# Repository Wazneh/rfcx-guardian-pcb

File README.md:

# rfcx-guardian-pcb
Hardware PCB designs for RFCx Guardians

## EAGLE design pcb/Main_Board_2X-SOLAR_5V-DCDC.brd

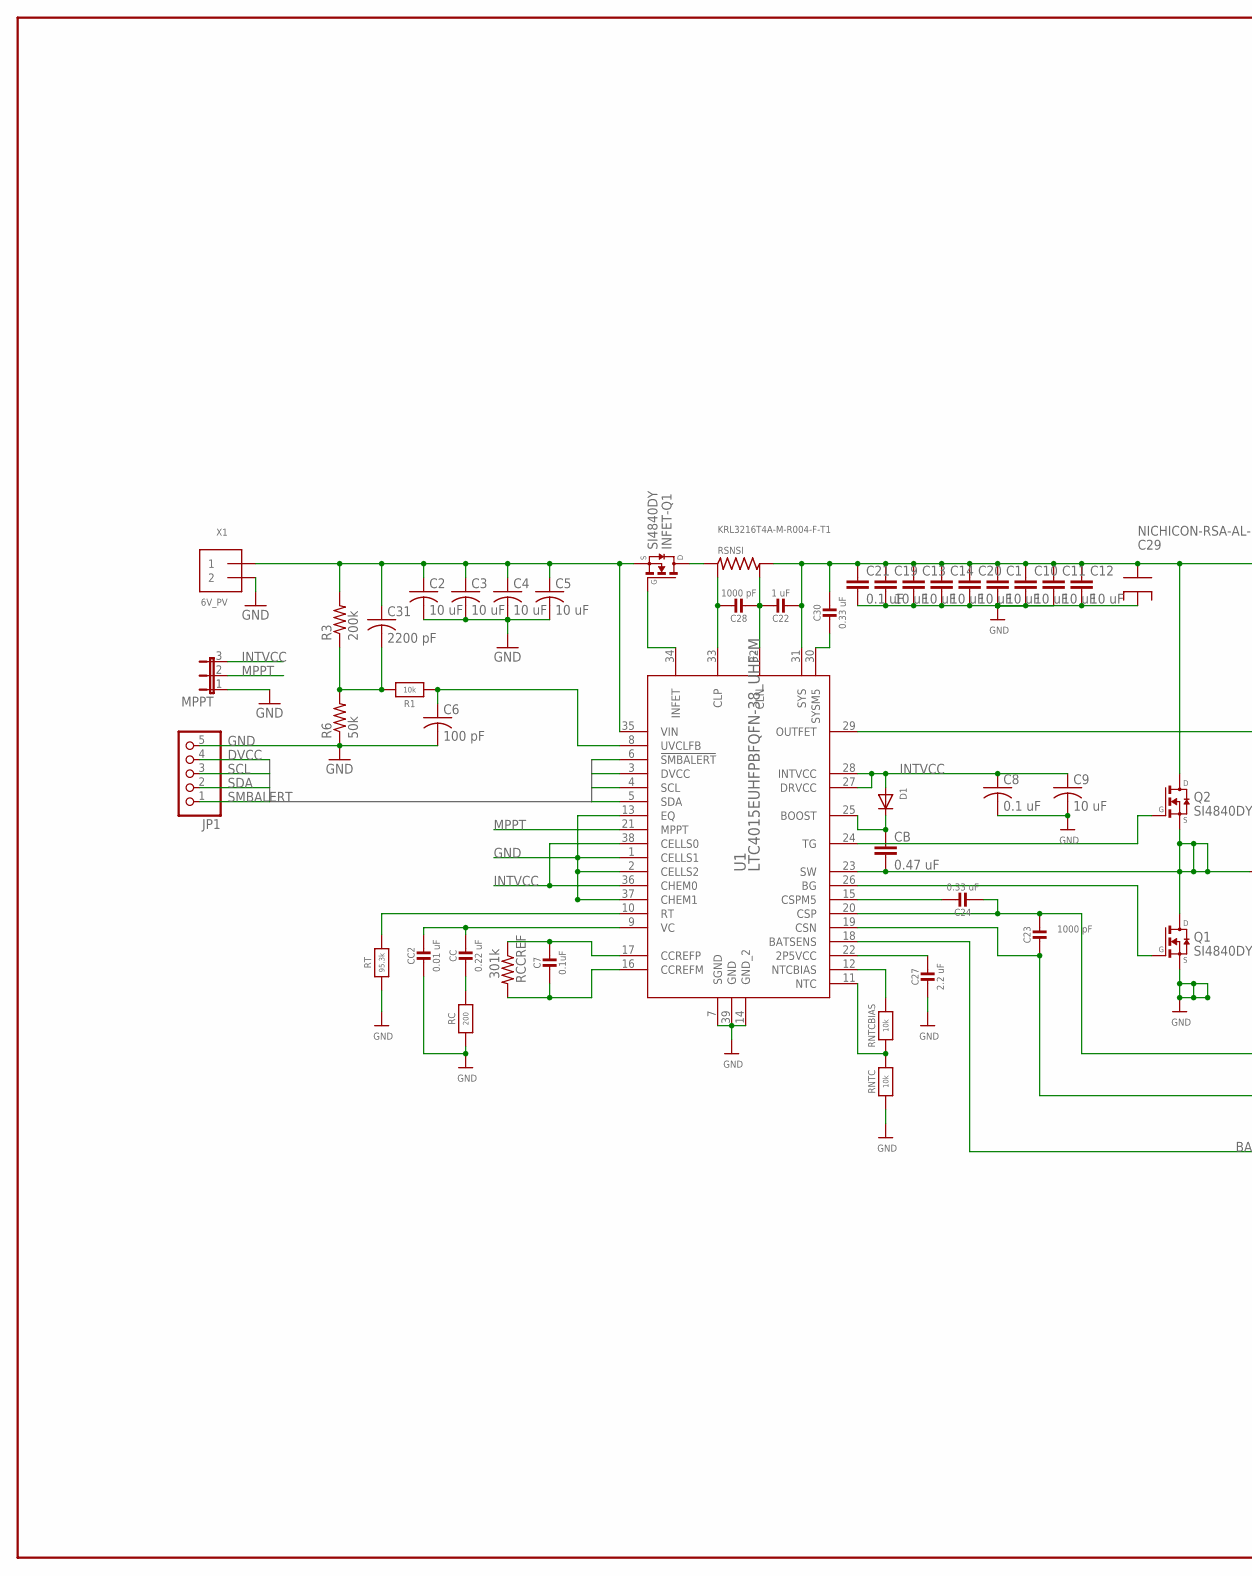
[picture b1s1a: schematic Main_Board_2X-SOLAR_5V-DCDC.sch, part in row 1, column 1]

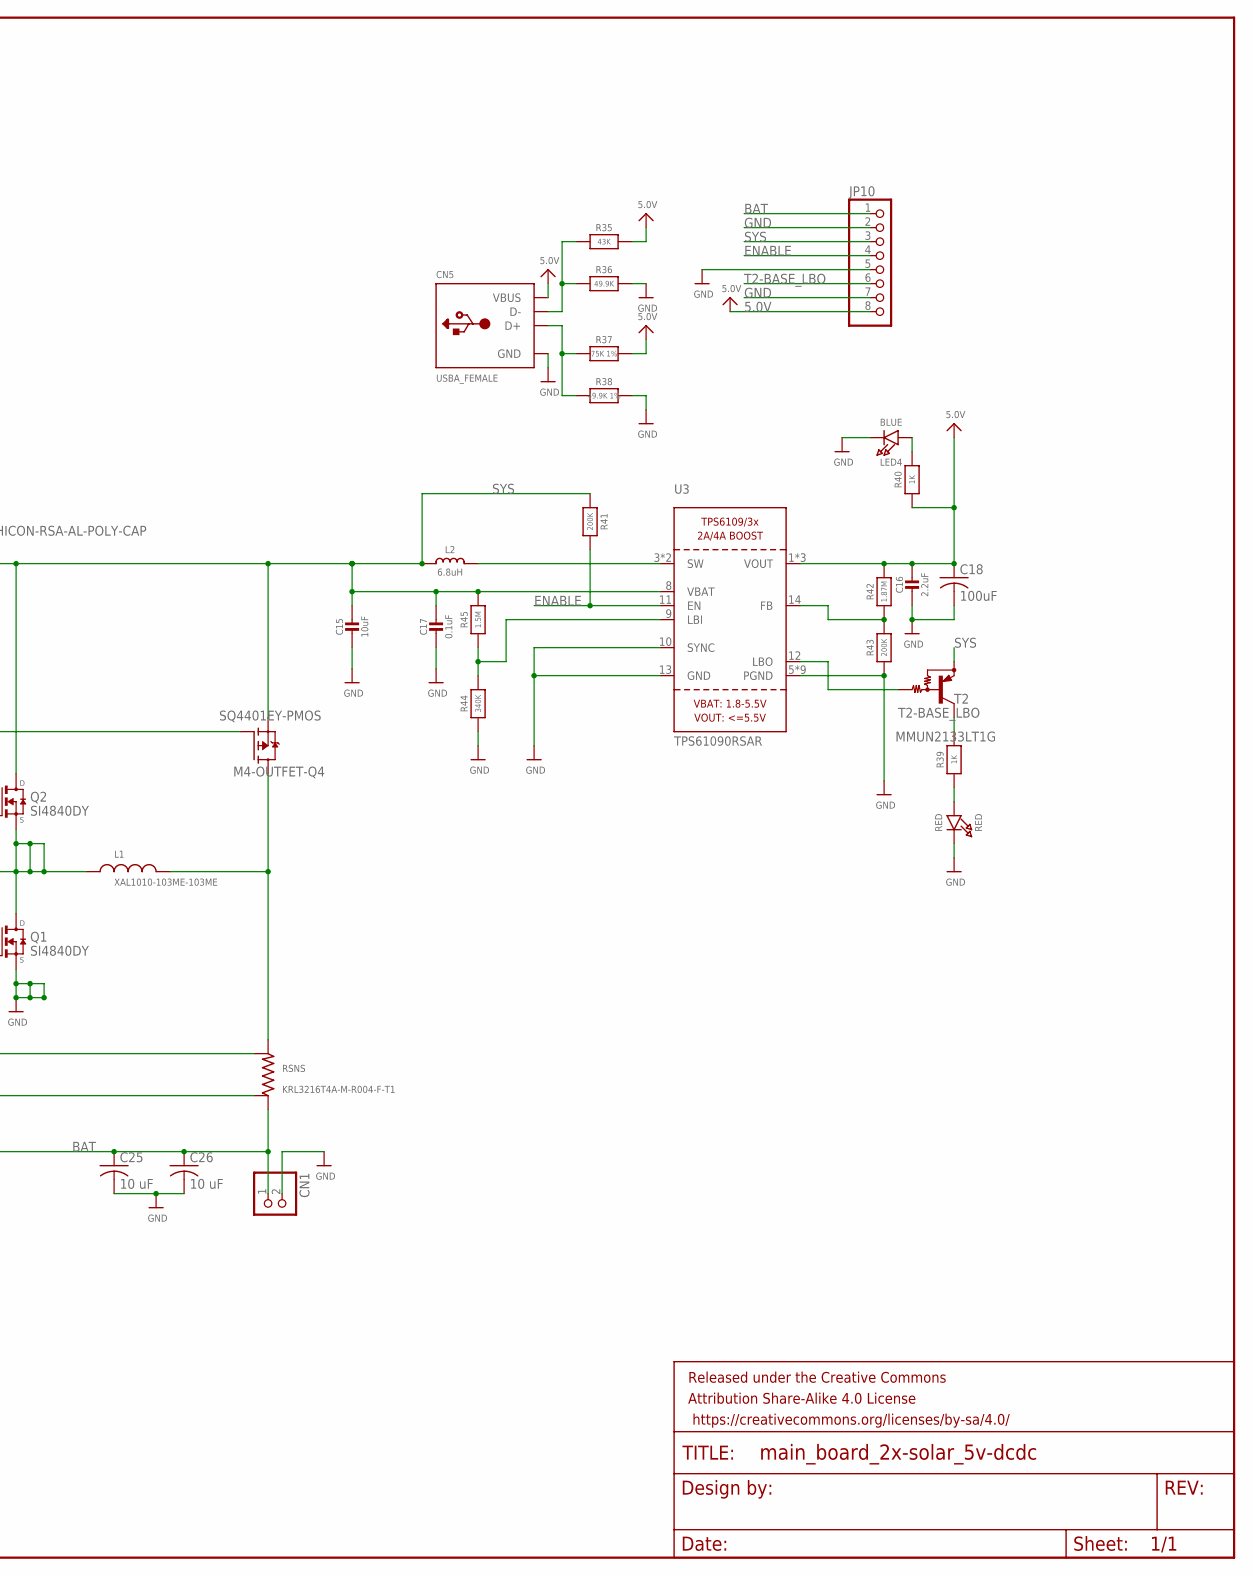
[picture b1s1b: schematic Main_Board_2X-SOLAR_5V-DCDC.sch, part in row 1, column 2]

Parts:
C1, C10, C11, C12, C13, C14, C19, C20, C25, C26: 10 uF; C1206
C2, C3, C4, C5, C9: 10 uF; C0805
C6: 100 pF; C0805
C7, C17: 0.1uF; 0805_10MGAP
C8: 0.1 uF; C0805
C15: 10uF; 0805-NO
C16: 2.2uF; 0805-NO
C18: 100uF; C1210
C21: 0.1 uF; C1206
C22: 1 uF; 0805-NO
C23, C28: 1000 pF; 0805-NO
C24, C30: 0.33 uF; 0805-NO
C27: 2.2 uF; 0805-NO
C29: NICHICON-RSA-AL-POLY-CAP; RSA-CAP-SMD
C31: 2200 pF; C0805
CB: 0.47 uF; C1206
CC: 0.22 uF; 0805-NO
CC2: 0.01 uF; 0805-NO
CN1: JST_2PIN-THM; JST-PH-2-THM
CN5: USBA_FEMALE; USB_HOST-PTH
D1: DIODESOD-123; SOD-123
FRAME1: FRAME-LEDGER; CREATIVE_COMMONS
INFET-Q1: SI4840DY; SO08-E3
JP1: PINHD-1X5; 1X05
JP10: HEADER-1X8ROUND; 1X08_ROUND
L1: XAL1010-103ME-103ME; XAL1010
L2: 6.8uH; INDUCTOR_5X5MM_TDK_VLC5045
LED4: BLUE; CHIPLED_0805_NOOUTLINE
M4-OUTFET-Q4: SQ4401EY-PMOS; SO08-E3
MPPT: JP2E; JP2
Q1, Q2: SI4840DY; SO08-E3
R1: 10k; _0805MP
R3: 200k; R0805
R6: 50k; R0805
R35: 43K; 0805-NO
R36: 49.9K; 0805-NO
R37: 75K 1%; 0805-NO
R38: 49.9K 1%; 0805-NO
R39, R40: 1K; 0805-NO
R41, R43: 200K; 0805-NO
R42: 1.87M; 0805-NO
R44: 340K; _0805MP
R45: 1.5M; _0805MP
RC: 200; 0805-NO
RCCREF: 301k; R0805
RED: RED; CHIPLED_0805_NOOUTLINE
RNTC: 10k; _0805MP
RNTCBIAS: 10k; _0805MP
RSNS: KRL3216T4A-M-R004-F-T1; 4-TERM-RESISTOR-SUMUSU
RSNSI: KRL3216T4A-M-R004-F-T1; 4-TERM-RESISTOR-SUMUSU
RT: 95.3k; 0805-NO
T2: MMUN2133LT1G; SC59-BEC
U1: LTC4015EUHFPBFQFN-38_UHF-M; QFN-38_UHF-M
U3: TPS61090RSAR; PVQFN-16
X1: 6V_PV; TERMBLOCK_1X2-3.5MM

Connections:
2P5VCC: C27.1, U1.22 (2P5VCC)
5.0V: C16.1, C18.1, CN5.VBUS, JP10.8, R35.2, R37.2, R40.1, R42.2, U3.1 (VOUT), U3.15 (VOUT), U3.16 (VOUT)
BAT: C25.1, C26.1, CN1.1 (2), JP10.1, RSNS.P$2 (2), U1.18 (BATSENS)
BG: Q1.4 (G), U1.26 (BG)
BOOST: CB.1, D1.C, U1.25 (BOOST)
CCREFM: C7.2, RCCREF.2, U1.16 (CCREFM)
CCREFP: C7.1, RCCREF.1, U1.17 (CCREFP)
CLN: C22.1, C28.2, RSNSI.P$4 (4), U1.32 (CLN)
CLP: C28.1, RSNSI.P$3 (3), U1.33 (CLP)
CSN: C23.2, RSNS.P$4 (4), U1.19 (CSN)
CSP: C23.1, C24.2, RSNS.P$3 (3), U1.20 (CSP)
CSPM5: C24.1, U1.15 (CSPM5)
D+1: CN5.D+, R37.1, R38.1
D-1: CN5.D-, R35.1, R36.1
DVCC: JP1.4, U1.3 (DVCC)
ENABLE: JP10.4, R41.2, U3.11 (EN)
FB: R42.1, R43.2, U3.14 (FB)
GND: C1.2, C2.2, C3.2, C4.2, C5.2, C6.2, C8.2, C9.2, C10.2, C11.2, C12.2, C13.2, C14.2, C15.2, C16.2, C17.2, C18.2, C19.2, C20.2, C21.2, C25.2, C26.2, C27.2, C29.P$1, CC2.2, CN1.2 (1), CN5.GND, JP1.5, JP10.2, JP10.5, JP10.7, LED4.C, MPPT.1, Q1.1-3 (S), R6.1, R36.2, R38.2, R43.1, R44.1, RC.1, RED.C, RNTC.1, RT.1, U1.1 (CELLS1), U1.2 (CELLS2), U1.7 (SGND), U1.13 (EQ), U1.14 (GND_2), U1.37 (CHEM1), U1.39 (GND), U3.5 (PGND), U3.6 (PGND), U3.7 (PGND), U3.10 (SYNC), U3.13 (GND), U3.P$18 (PGND), U3.P$19 (PGND), U3.P$20 (PGND), U3.P$21 (PGND), U3.P$22 (PGND), U3.THERMAL (PGND), X1.2
INFET: INFET-Q1.4 (G), U1.34 (INFET)
INTVCC: C8.1, C9.1, D1.A, MPPT.3, U1.27 (DRVCC), U1.28 (INTVCC), U1.36 (CHEM0), U1.38 (CELLS0)
LBI: R44.2, R45.1, U3.9 (LBI)
LED+: LED4.A, R40.2
MPPT: MPPT.2, U1.21 (MPPT)
unnamed: R39.1, RED.A
unnamed: INFET-Q1.5-8 (D), RSNSI.P$1 (1)
unnamed: C6.1, R1.1, U1.8 (UVCLFB)
unnamed: CC.2, RC.2
unnamed: RNTC.2, RNTCBIAS.1, U1.11 (NTC)
NTCBIAS: RNTCBIAS.2, U1.12 (NTCBIAS)
OUTFET: M4-OUTFET-Q4.4 (G), U1.29 (OUTFET)
OUTFET_M4_BAT: L1.P$2, M4-OUTFET-Q4.5-8 (D), RSNS.P$1 (1)
RT: RT.2, U1.10 (RT)
SCL: JP1.3, U1.4 (SCL)
SDA: JP1.2, U1.5 (SDA)
SMBALERT: JP1.1, U1.6 (!SMBALERT)
SW: L2.P$2 (2), U3.3 (SW), U3.4 (SW)
SW_LTC: CB.2, L1.P$1, Q1.5-8 (D), Q2.1-3 (S), U1.23 (SW)
SYS: C1.1, C10.1, C11.1, C12.1, C13.1, C14.1, C15.1, C17.1, C19.1, C20.1, C21.1, C22.2, C29.P$2, C30.1, JP10.3, L2.P$1 (1), M4-OUTFET-Q4.1-3 (S), Q2.5-8 (D), R41.1, R45.2, RSNSI.P$2 (2), T2.E, U1.31 (SYS), U3.8 (VBAT)
SYSM5: C30.2, U1.30 (SYSM5)
T2-BASE_LBO: JP10.6, T2.B, U3.12 (LBO)
T2-DRAIN: R39.2, T2.C
TG: Q2.4 (G), U1.24 (TG)
UVCLFB: C31.2, R1.2, R3.1, R6.2
VC: CC.1, CC2.1, U1.9 (VC)
VIN: C2.1, C3.1, C4.1, C5.1, C31.1, INFET-Q1.1-3 (S), R3.2, U1.35 (VIN), X1.1

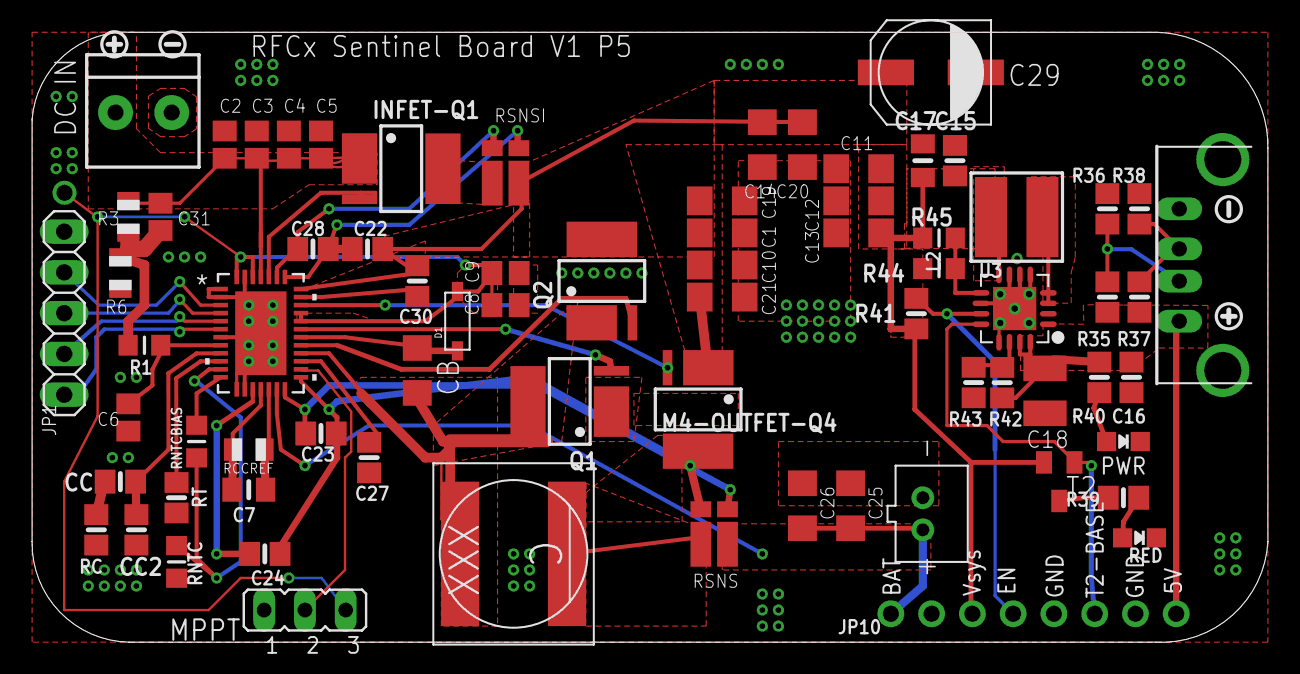
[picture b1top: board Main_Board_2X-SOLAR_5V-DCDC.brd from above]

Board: 2 copper layers, 77.0 x 38.0 mm, 78 parts (0 on the bottom side), 45 nets.

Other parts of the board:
U$2, U$86: SYMBOL_PLUS
U$13, U$87: SYMBOL_MINUS

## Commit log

2017-05-31 Basic initial main board
    PCB and schematic layout of 2 solar battery chargers mostly completed. Copied 5V D/DC step-up into project. Need to add jumpers and complete routing for diodes and capacitors on solar battery charger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
2017-06-01 Added 5V board and fixed PCB layout
    Added 5V step up board loayout to main PCB. Removed additional MCP module from 5V layout.
2017-06-02 PCB manufacturing and assembly quotes
    Adding quotes from different PCB services
2017-06-05 Completed board layout
    Completed layout for 2 MCP chips and TI 5V step-up boost. MCP load outputs merged and routed to 5V step-up, no 5V power wires needed. Added terminal block option for solar panel input. Added BOM fold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
2017-06-06 PCB board rev 1
    Files used to print prototype from bayareacircuits. Adding BOM file and CAM/GERBER files
2017-06-07 Rev 2 start
    Removed extra USB mounts, jumpers, and headers. BOM completed but missing a couple items from Digikey
2017-06-07 Final BOM
    Updated BOM to final
2017-06-08 updated bom
2017-06-08 updated original rev 0 board
    commiting to master to save all files from first print
2017-06-08 reorganization of files for rev 2
    moved gerber files to seperate folder
2017-06-08 Part removal and gitignore update
    removed more jumpers and headers and updated the ignore file to ignore autosave files
2017-06-11 Added jumpers and diodes to load line regulation
2017-06-11 Removal of extra files
    Moved Gerber files to serperate folder
2017-06-13 Cleaned up silkscreen
    Moved silkscreen for better visibility during assembly and deleted extra labels. Shrank board a little bit smaller in dimension
2017-06-15 updated layout and BOM
2017-06-20 BOM update
2017-07-02 OSH revision. No jumpers, compressed layout
    Shrank the layout of the board to a smaller size and removed the jumpers for easier assembly
2017-07-13 updated BOM
    Updated BOM to match new layout. Removed a few resistors and consolidated duplicate line items
2017-07-16 Added LT4015 footprints to eagle and began routing
    LTC4015 chip footprints and schematic uploaded to eagle library. Routing started for new board. Removed all routings so only airwires exist at this point.
2017-07-19 Footprint added and began LTC4015 layout
    Created LTC4015 footprint in library and schematic. Updated BOM for original board with prices for each part and consolidated parts
2017-07-19 BOM update
    Removed extra USB connectors not used in design
2017-07-19 Updated BOM for master repo
    BOM updated to match board layout and added prices
2017-07-19 BOM additions and adjustments
    Added vertical USB-A female receptacle
2017-07-24 Updated BOM and layout for LTC4015
    Schematic pinout redone for LTC4015 part to match design application guide and make schematic easier to follow. Schematic and board routing started. BOM updated and consolidated for last revision of 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
2017-07-25 Bom update
    Minor formatting update
2017-07-26 Updated library, schematic, and board layout
    Added new components to library and continuing to update schematic and board
2017-07-28 New BOM for LiFePO4 board and updated sch/brd
2017-07-28 added more components
2017-07-29 Sch/Brd update, added image for silkscreen
2017-08-01 Board layout finished
    PCB board layout finished. Final errors to review are related to package pad clearances.
2017-08-02 PCB ready to print, reviewing
2017-08-02 OSH V1 print board and schematic update
    Finalized routings for signal and power. Updated silkscreen text for clarity during assembly.
2017-08-07 BOM updates and component coordinates file (mnt)
2017-08-07 updaled to new BOM for assembly and regenerated gerber files
2017-08-11 updated GERBER zip with outline file
    Added GKO outline file to GERBER
2017-08-14 Updated schematic with UVCLFB input
    added 10k resistor
2017-08-14 Updated BOM for R1
    Updated diode part list to match quantity
2017-08-14 Updated schematic text
    Updated labels in schematic to reduce clutter
2017-08-25 Updates to schematic and board layout to fix V1
2017-08-25 Updated schematic and board layout for V1
    Added jumper for VIN and updated footprint for 8030 package
2017-08-25 OSH print V1 P2
2017-09-12 Fixed NTC resistor routing
    Added 10k NTC resistor to NTC pin and added INTVCC output to jumpers. Updated silkscreens for easier reading
2017-09-13 Sentinel Board V1P3
    Updated silkscreen and added MPPT switch to allow for logic level/pin selection for MPPT instead of i2c only.
2017-09-19 Sentinel V1 P4 updated layout
    Fixed schematic and board layout for easier assembly and corrected connection to M3AB NMOS pair.
2017-09-23 Updated layout
2017-09-23 Updated Sentinel Board with larger FETs
2017-09-27 Updated layout sizing, ground plane thermals, and silkscreen positions
    Shrank board size slightly and aligned edges. Made component silk screens easier to read and adjusted ground planes on Csys and INT/DRVcc GND

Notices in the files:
parts and their libraries:
SparkFun-Aesthetics: Licensing: Creative Commons ShareAlike 4.0 International - https://creativecommons.org/licenses/by-sa/4.0
SparkFun-Aesthetics: Released under the Creative Commons Attribution Share-Alike 4.0 License
SparkFun-Aesthetics: https://creativecommons.org/licenses/by-sa/4.0
